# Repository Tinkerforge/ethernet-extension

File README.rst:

Ethernet Extension
==================

This repository contains the hardware design files.
The software is included in the Master Brick software
and can be found at https://github.com/Tinkerforge/master-brick

Repository Content
------------------

hardware/:
 * Contains KiCad project files and additionally schematics as PDF

datasheets/:
 * Contains datasheets for sensors and complex ICs that are used

Hardware
--------

The hardware is designed with the open source EDA Suite KiCad
(http://www.kicad.org). Before you are able to open the files,
you have to install the Tinkerforge kicad-libraries
(https://github.com/Tinkerforge/kicad-libraries). You can either clone
them directly in hardware/ or clone them in a separate folder and
symlink them into hardware/
(ln -s kicad_path/kicad-libraries project_path/hardware). After that you
can open the .pro file in hardware/ with KiCad and from there view and
modify the schematics and the PCB layout.

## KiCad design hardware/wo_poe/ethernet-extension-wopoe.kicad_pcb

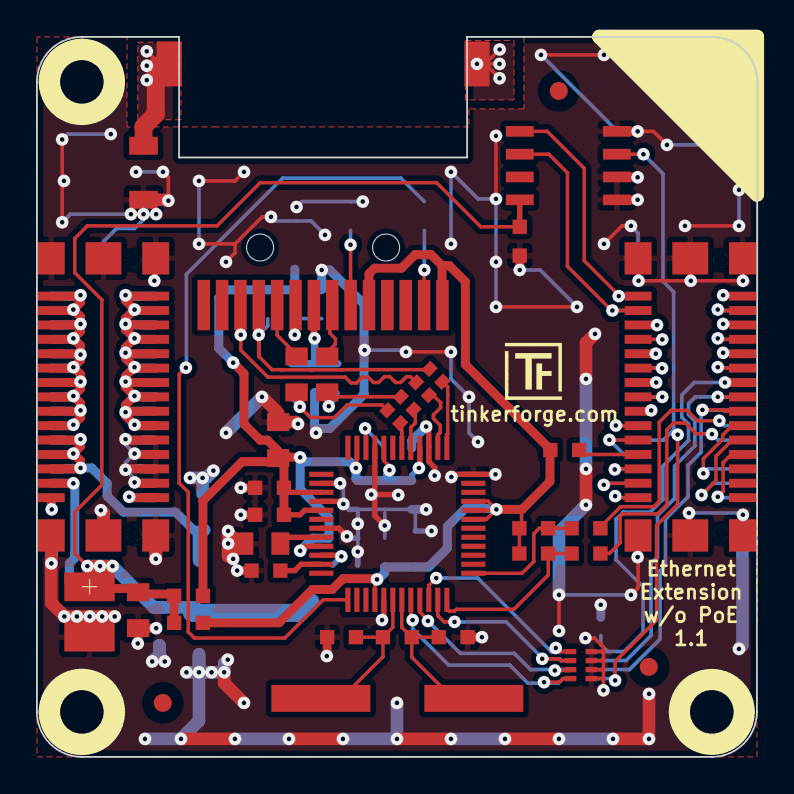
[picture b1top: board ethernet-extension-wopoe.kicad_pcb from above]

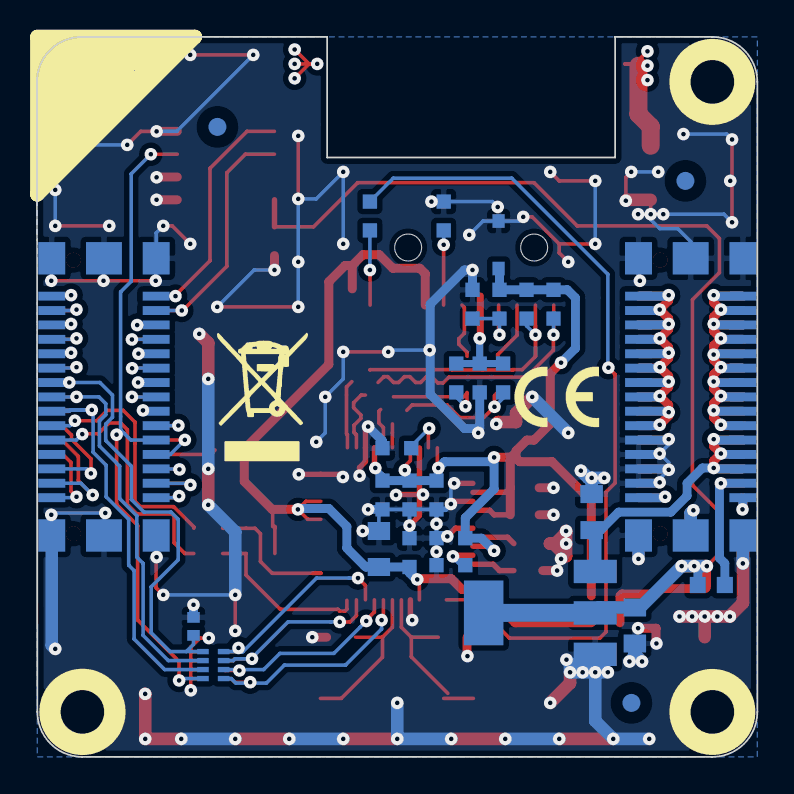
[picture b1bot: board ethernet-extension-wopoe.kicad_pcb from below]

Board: 2 copper layers, 40.0 x 40.0 mm, 70 parts (33 on the bottom side), 68 nets.

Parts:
C1, C4, C13: 10µF/16V-TT; 0805P
C2, C17: 10nF; C0603
C3, C5, C6, C7, C8, C10, C11, C20: 100nF; C0603
C9, C102, C103: 4.7uF; C0805
C12, C15: 10pF; C0603
C14: 100µF; 3528-21
C16: 22nF; C0603
C18, C19: 6.8nF; C0805
C21: 1nF/2kV; C1206
C101: 10pF; C0402F
D101: ‎PESD3V3L1BA; SOD-323
Fiducial_Mark: VAL**; Fiducial_Mark
Fiducial_Mark#2, Fiducial_Mark#3, Fiducial_Mark#4, Fiducial_Mark#5, Fiducial_Mark#6: VAL**; Fiducial_Mark
J1, J3: STACK-UP-HIGH; BTB08-ACS-TOP
J2, J4: STACK-DOWN; BTB08-ACS-BTM
L1, L2: FB; C0603
L101: TBD; R0603F
P1: RJPSL-001TA1
R1, R3: 10k; R0603
R2, R106: DNP; R0603
R5: 12.4k 1%; R0603
R6: 1M; R0603
R7, R8, R10, R11: 49.9; R0603
R9: 10; R0603
R12, R13: 470; R0603
R14, R105: 1k; R0603
R101, R102, R103, R104: 33; R0402F
RP102: 82; 4X0402
RP103: DNP; 4X0402
U1: W5500; LQFP48
U2: M24C64; SOIC8
U3, U4, U5, U6: DRILL; DRILL_NP
U101: AZ1117-3V3; SOT-223
VAL: WEEE_7mm
VAL#2: CE_5mm
X1: 25Mhz; HC49_US

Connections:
3V3: C1.1, C3.2, L1.1, P1.8, P1.14, R1.2, R2.2, R14.1, U1.28, U1.43, U1.44, U1.45
+3.3VP: C4.1, C5.2, C6.2, C7.2, C8.2, C10.2, C11.2, D101.1, L2.1, R7.1, R8.1, R9.1, U1.4, U1.8, U1.11, U1.15, U1.17, U1.21
GND: C1.2, C2.1, C3.1, C4.2, C5.1, C6.1, C7.1, C8.1, C9.1, C10.1, C11.1, C12.1, C13.2, C14.2, C15.1, C16.1, C17.1, C20.1, C21.2, C101.1, C102.1, C103.1, D101.2, J1.EP, J2.EP, J3.21, J3.23, J3.25, J3.27, J3.EP, J4.21, J4.23, J4.25, J4.27, J4.EP, R3.1, R5.1, R12.1, RP103.1, RP103.2, RP103.3, RP103.4, U1.3, U1.9, U1.14, U1.16, U1.19, U1.29, U1.48, U2.1, U2.2, U2.4, U101.1
INT: J2.21, R106.1
MISO: C101.2, J1.13, J2.13, RP102.1
MOSI: J1.15, J2.15, RP102.2
unnamed: C2.2, U1.22
unnamed: C9.2, U1.20
unnamed: C12.2, R6.1, U1.31, X1.1
unnamed: C15.2, R6.2, U1.30, X1.2
unnamed: C16.2, P1.4, R9.2
unnamed: C17.2, P1.5, R10.2, R11.1
unnamed: C18.1, R10.1, R103.1
unnamed: C18.2, P1.3
unnamed: C19.1, R11.2, R104.1
unnamed: C19.2, P1.6
unnamed: J1.1, J2.1
unnamed: J1.3, J2.3
unnamed: J1.5, J2.5
unnamed: J1.6, J2.6
unnamed: J1.7, J2.7
unnamed: J1.8, J2.8
unnamed: J1.9, J2.9
unnamed: J1.10, J2.10
unnamed: J1.11, J2.11
unnamed: J1.12, J2.12
unnamed: J1.14, J2.14
unnamed: J1.16, J2.16
unnamed: J1.18, J2.18
unnamed: J1.19, J2.25
unnamed: J1.20, J2.20
unnamed: J1.21, J2.27
unnamed: J1.22, J2.24
unnamed: J1.23, J2.29
unnamed: J1.24, R14.2
unnamed: J1.26, J2.26
unnamed: J1.28, J2.28
unnamed: J1.30, J2.30
unnamed: J3.1, J3.3, J3.5, J3.7, J3.9, J3.11, J3.13, J3.15, J3.17, J3.19, J4.1, J4.3, J4.5, J4.7, J4.9, J4.11, J4.13, J4.15, J4.17, J4.19
unnamed: J3.2, J3.4, J3.6, J3.8, J3.10, J3.12, J3.14, J3.16, J3.18, J3.20, J4.2, J4.4, J4.6, J4.8, J4.10, J4.12, J4.14, J4.16, J4.18, J4.20
unnamed: J3.29, J4.29
unnamed: J3.30, J4.30
unnamed: P1.1, R7.2, R101.1
unnamed: P1.2, R8.2, R102.1
unnamed: P1.7, R12.2
unnamed: P1.13, R13.2
unnamed: R1.1, R105.2, U1.37
unnamed: R3.2, U1.23
unnamed: R5.2, U1.10
unnamed: R2.1, R106.2, U1.36
unnamed: RP102.5, RP103.8, U1.32
unnamed: RP102.6, RP103.7, U1.33
unnamed: RP102.7, RP103.6, U1.35
unnamed: RP102.8, RP103.5, U1.34
RXIN: R104.2, U1.5
RXIP: R103.2, U1.6
S3V3: J3.28, J4.28, L101.1
S5V: C102.2, J3.22, J3.24, J3.26, J4.22, J4.24, J4.26, U101.3
SCK: J1.17, J2.17, RP102.3
SCL: J1.4, J2.4, U2.6
SDA: J1.2, J2.2, U2.5
SELECT: J2.22, RP102.4, U2.3
SHD: C21.1, P1.SHD
TXON: R102.2, U1.1
TXOP: R101.2, U1.2
VCC: C13.1, C14.1, C20.2, C103.2, L1.2, L2.2, L101.2, U2.8, U101.2
nRESET: J2.19, R105.1
yellowLED: R13.1, U1.25

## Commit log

2013-04-12 Initial Ethernet Extension commit
2013-04-12 Fix typo
2013-05-23 add kicad design files and schematic for ethernet extension
2013-06-06 Add Ethernet Extension W5200 datasheet
2015-06-23 add hardware files for ethernet extension wo poe
2015-06-23 add hardware files for new ethernet extension with W5500 and PoE
2015-06-23 add missing file
2015-06-23 remove tinkerforge.com text on bottom
2015-09-28 adapt mosfet series gate resistor
2016-04-26 fix schematic
2017-04-20 fix some value texts
2017-07-20 fix schematic symbols
2017-07-20 make color schematic
2017-07-20 add schematic for non poe version
2017-07-20 add w5500 datasheet
2017-07-20 fix schematic naming
2017-07-20 remove files of old version
2017-08-03 Add 3d information (final)
2017-08-03 Add 3d model (*.step & *.FCStd)
2017-08-03 Add 3d information (tbc)
2017-08-04 Rename files
2017-08-04 Undo renaming
2018-05-11 PoE: rename files
2018-05-11 w/o PoE: Rename files
2020-05-25 fix library settings
2020-05-27 add version 1.2 proto files
2020-12-08 version 1.2
2020-12-08 specify reference
2020-12-08 specify stuff
2021-10-25 Update KiCad link
    https://www.kicad.org/blog/2021/10/Avoid-links-to-former-kicad-domain/
2022-09-06 add data of ethernet extension 1.1
    move to kicad 6

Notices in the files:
hardware/wo_poe/ethernet-extension-wopoe.kicad_pcb:
Licensed under CERN OHL v.1.1
Copyright (©) 2015, B.Nordmeyer
Copyright Tinkerforge GmbH 2020.
This documentation describes Open Hardware and is licensed under the
CERN OHL v. 1.1.
